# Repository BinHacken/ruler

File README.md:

# PCB Ruler "Bright Start"

Ein Platinen Lineal für die Ersti-Tüte der TH Bingen 2025. 
Mit kleinen cheat-sheets für die Informatik Studierenden.

Kann zu einer LED Lampe umgebaut werden. 

## Components

- PCB (Das Lineal selbst)
- 3x LED Filament 3V 38mm (D1,D2,D3)
- 1x USB-C Buchse 6-Pin (J1)
- 6x Wiederstände 1206
    - 3x 22Ω (R1,R2,R3)
    - 1x 51Ω (R4)
    - 2x 5.1KΩ (R5,R6)
- 1x 7pin toggle switch (SW1)

Für R1,R2,R3 und R4 können auch höhere Widerstandswerte verwendet werden, um die Helligkeit zu verringern. 
R5 und R6 sind für USB und sollten 5.1KΩ haben (im Notfall gehen auch 4.7KΩ – 5.6KΩ). 

Der Schalter (SW1) ist dafür da zwischen 2 Helligkeitsstufen zu wählen. 
Wer stattdessen einen an/aus Schalter bevorzugt, kann R4 weglassen. 

Wir haben die passenden Bauteile und Werkzeug parat, komm gerne vorbei! https://binhacken.de/ 

## Placement

Es empfiehlt sich, die Bauteile wie folgt auf der Platine zu platzieren:

1. Die USB-C Buchse (**J1**) und der 7pin toggle switch (**SW1**). 
2. Die Widerstände (R1-R6)
3. Die LEDs (D1-D3)

Wer wenig Erfahrung mit Löten hat, kann auch gerne mit einem der Widerstände (R1-R6) beginnen, da diese in der Regel einfacher zu löten sind. Auch wenn die USB-C Buchse und der Schalter etwas anspruchsvoller zu löten sind, sollten sie nicht zuletzt platziert werden, da die kleinen Pads sonst schwerer zugänglich sind.

Eine Interaktive Ansicht der Platine gibt es hier: https://htmlpreview.github.io/?https://github.com/BinHacken/ruler/blob/main/bom/ibom.html

## Ordering

Folgende Optionen haben wir bei JLC gewählt:

* Deburring/Edge rounding: Yes
* PCB Thickness: 1mm
* Surface Finish: Leadfree HASL
* Mark on PCB: Remove Mark

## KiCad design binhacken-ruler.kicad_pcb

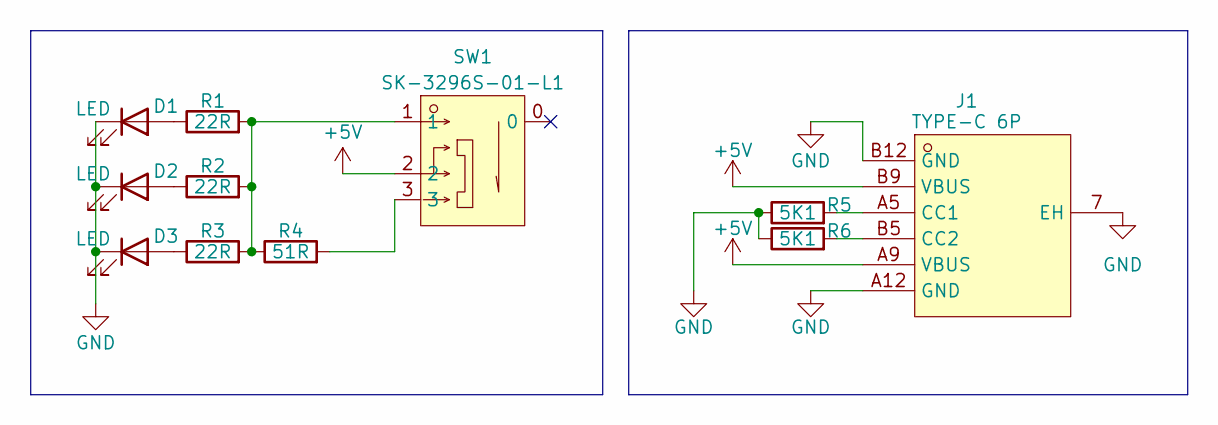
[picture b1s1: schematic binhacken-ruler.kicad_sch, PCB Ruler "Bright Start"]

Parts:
D1, D2, D3: LED; LED_Filament_38mm
J1: TYPE-C 6P; TYPE-C-SMD_TYPE-C-6P; LCSC Part C456012
R1, R2, R3: 22R; R_1206_3216Metric_Pad1.30x1.75mm_HandSolder
R4: 51R; R_1206_3216Metric_Pad1.30x1.75mm_HandSolder
R5, R6: 5K1; R_1206_3216Metric_Pad1.30x1.75mm_HandSolder
SW1: SK-3296S-01-L1; SW-SMD_3P-P1.50_L2.7-W6.6; LCSC Part C319020

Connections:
+5V: J1.A9 (VBUS), J1.B9 (VBUS), SW1.2
GND: D1.1 (K), D2.1 (K), D3.1 (K), J1.7 (EH), J1.A12 (GND), J1.B12 (GND), R5.1, R6.1
unnamed: D1.2 (A), R1.1
unnamed: D2.2 (A), R2.1
unnamed: D3.2 (A), R3.1
unnamed: R1.2, R2.2, R3.2, R4.1, SW1.1
unnamed: R4.2, SW1.3
unnamed: J1.A5 (CC1), R5.2
unnamed: J1.B5 (CC2), R6.2

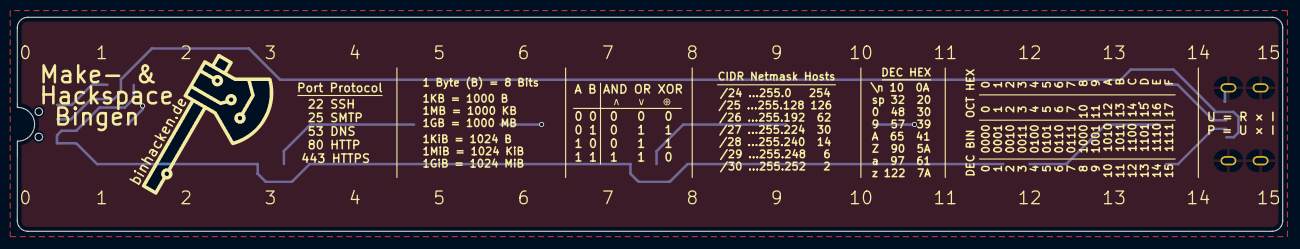
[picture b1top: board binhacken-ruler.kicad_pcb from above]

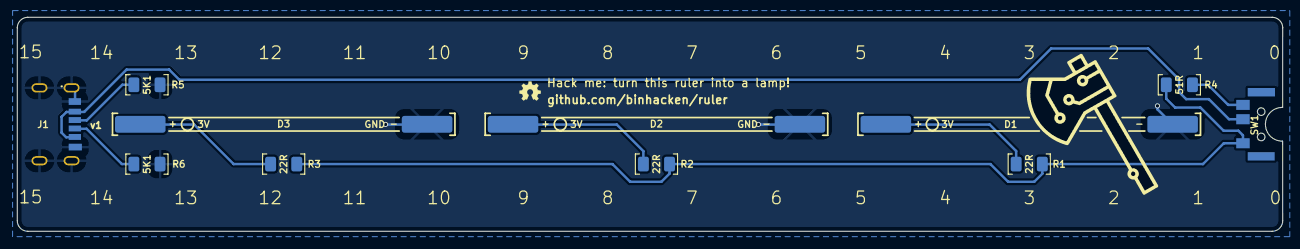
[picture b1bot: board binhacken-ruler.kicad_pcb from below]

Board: 2 copper layers, 150.0 x 25.4 mm, 11 parts (11 on the bottom side), 9 nets.

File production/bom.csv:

Designator,Footprint,Quantity,Value,LCSC Part #
"D1, D2, D3",LED_Filament_38mm,3,LED,
J1,TYPE-C-SMD_TYPE-C-6P,1,TYPE-C 6P,C456012
"R1, R2, R3",1206,3,22R,
R4,1206,1,51R,
"R5, R6",1206,2,5K1,
SW1,SW-SMD_3P-P1.50_L2.7-W6.6,1,SK-3296S-01-L1,C319020

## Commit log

2025-09-01 Initial Project Progress
2025-09-01 Order notes
